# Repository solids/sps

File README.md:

sps
===

solids pressure sensitive buttons

## brain
[This is](https://github.com/solids/sps/blob/master/brain/brain.ino) an arduino sketch running on an arduino uno

## circuit

[This is] (https://github.com/solids/sps/tree/master/circuit) the latest board/schematic sensor design (designed in eagle)

## node

[This is] (https://github.com/solids/sps/tree/master/node) the code that runs on the physical board defined in the circuit folder.

Currently I2C is used for the bus, but we may migrate to chained SPI for less protocol
overhead.

## License

[MIT](http://tmpvar.mit-license.org)

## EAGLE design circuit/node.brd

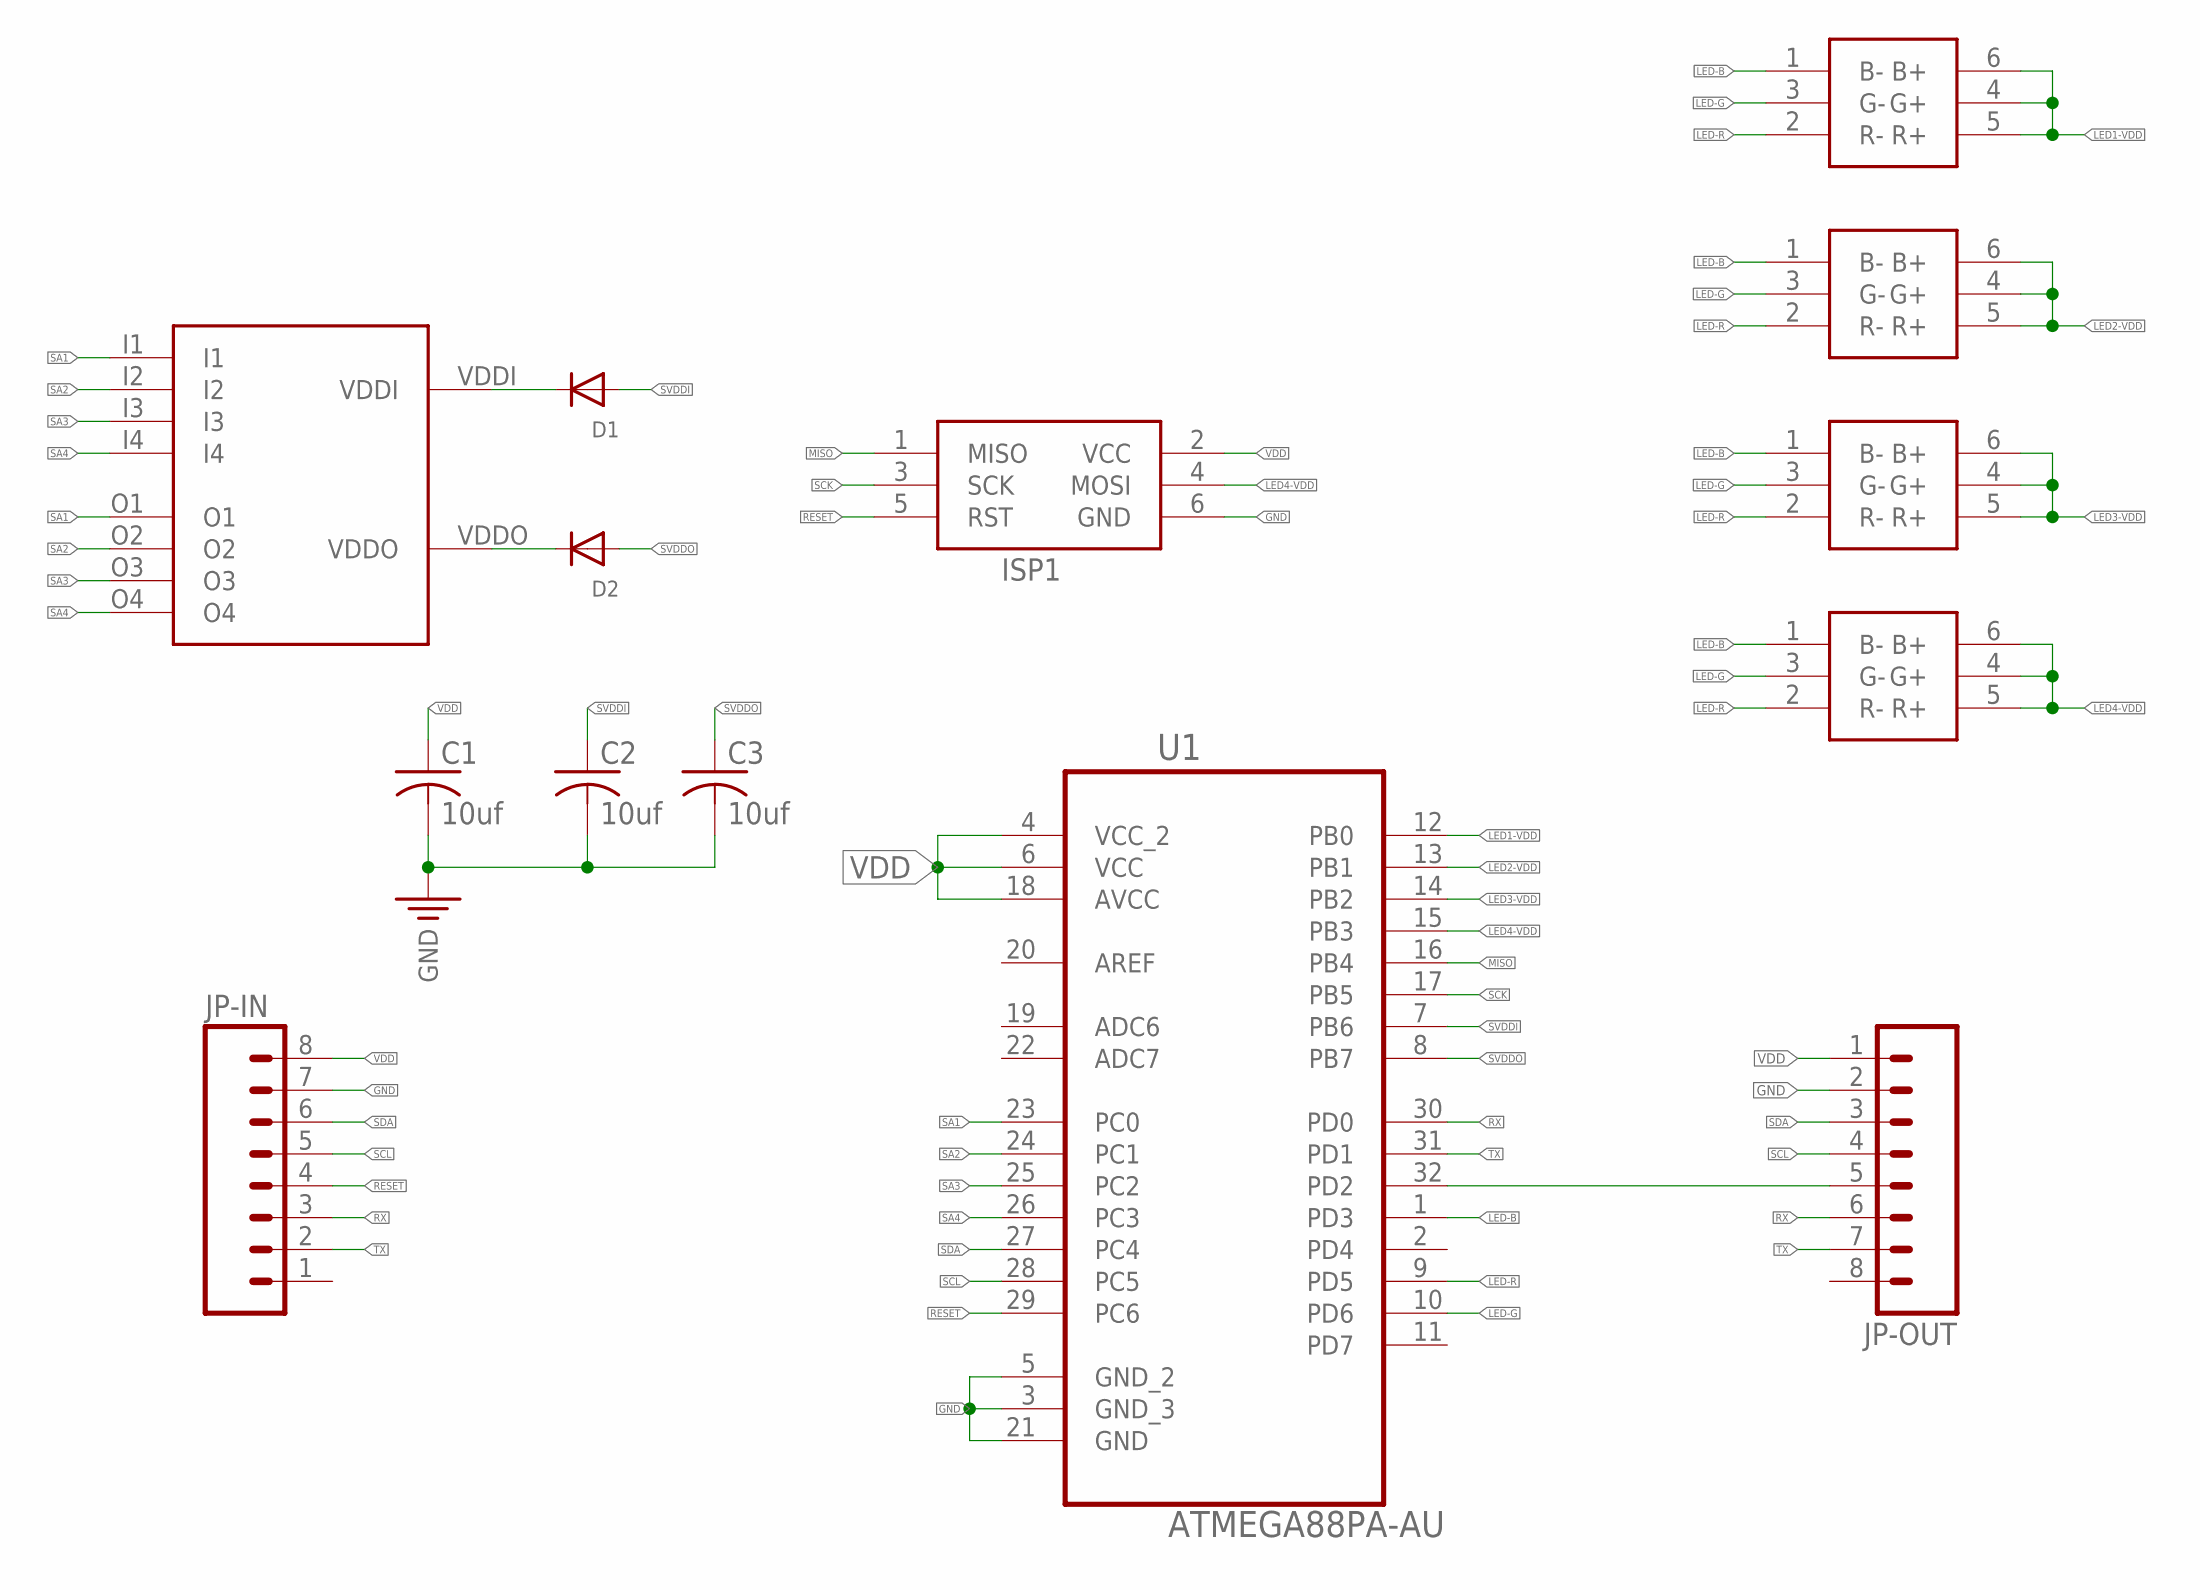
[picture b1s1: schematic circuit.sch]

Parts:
C1, C2, C3: 10uf; C0805K
D1, D2: DIODESOD-323F; SOD-323F
ISP1: AVRISP-6; AVRISP
JP-IN: M08LONGPADS; 1X08_LONGPADS
JP-OUT: M08LONGPADS; 1X08_LONGPADS
LED1, LED2, LED3, LED4: SMT-RGB-6PLCC
U1: ATMEGA88PA-AU; QFP80P900X900X120-32N
U$2: SPS8-0.0.1

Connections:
GND: C1.2, C2.2, C3.2, ISP1.6 (GND), JP-IN.7, JP-OUT.2, U1.3 (GND_3), U1.5 (GND_2), U1.21 (GND)
LED1-VDD: LED1.4 (G+), LED1.5 (R+), LED1.6 (B+), U1.12 (PB0)
LED2-VDD: LED2.4 (G+), LED2.5 (R+), LED2.6 (B+), U1.13 (PB1)
LED3-VDD: LED3.4 (G+), LED3.5 (R+), LED3.6 (B+), U1.14 (PB2)
LED4-VDD: ISP1.4 (MOSI), LED4.4 (G+), LED4.5 (R+), LED4.6 (B+), U1.15 (PB3)
LED-B: LED1.1 (B-), LED2.1 (B-), LED3.1 (B-), LED4.1 (B-), U1.1 (PD3)
LED-G: LED1.3 (G-), LED2.3 (G-), LED3.3 (G-), LED4.3 (G-), U1.10 (PD6)
LED-R: LED1.2 (R-), LED2.2 (R-), LED3.2 (R-), LED4.2 (R-), U1.9 (PD5)
MISO: ISP1.1 (MISO), U1.16 (PB4)
unnamed: D1.C, U$2.VDDI
unnamed: D2.C, U$2.VDDO
unnamed: JP-OUT.5, U1.32 (PD2)
RESET: ISP1.5 (RST), JP-IN.4, U1.29 (PC6)
RX: JP-IN.3, JP-OUT.6, U1.30 (PD0)
SA1: U1.23 (PC0), U$2.I1, U$2.O1
SA2: U1.24 (PC1), U$2.I2, U$2.O2
SA3: U1.25 (PC2), U$2.I3, U$2.O3
SA4: U1.26 (PC3), U$2.I4, U$2.O4
SCK: ISP1.3 (SCK), U1.17 (PB5)
SCL: JP-IN.5, JP-OUT.4, U1.28 (PC5)
SDA: JP-IN.6, JP-OUT.3, U1.27 (PC4)
SVDDI: C2.1, D1.A, U1.7 (PB6)
SVDDO: C3.1, D2.A, U1.8 (PB7)
TX: JP-IN.2, JP-OUT.7, U1.31 (PD1)
VDD: C1.1, ISP1.2 (VCC), JP-IN.8, JP-OUT.1, U1.4 (VCC_2), U1.6 (VCC), U1.18 (AVCC)

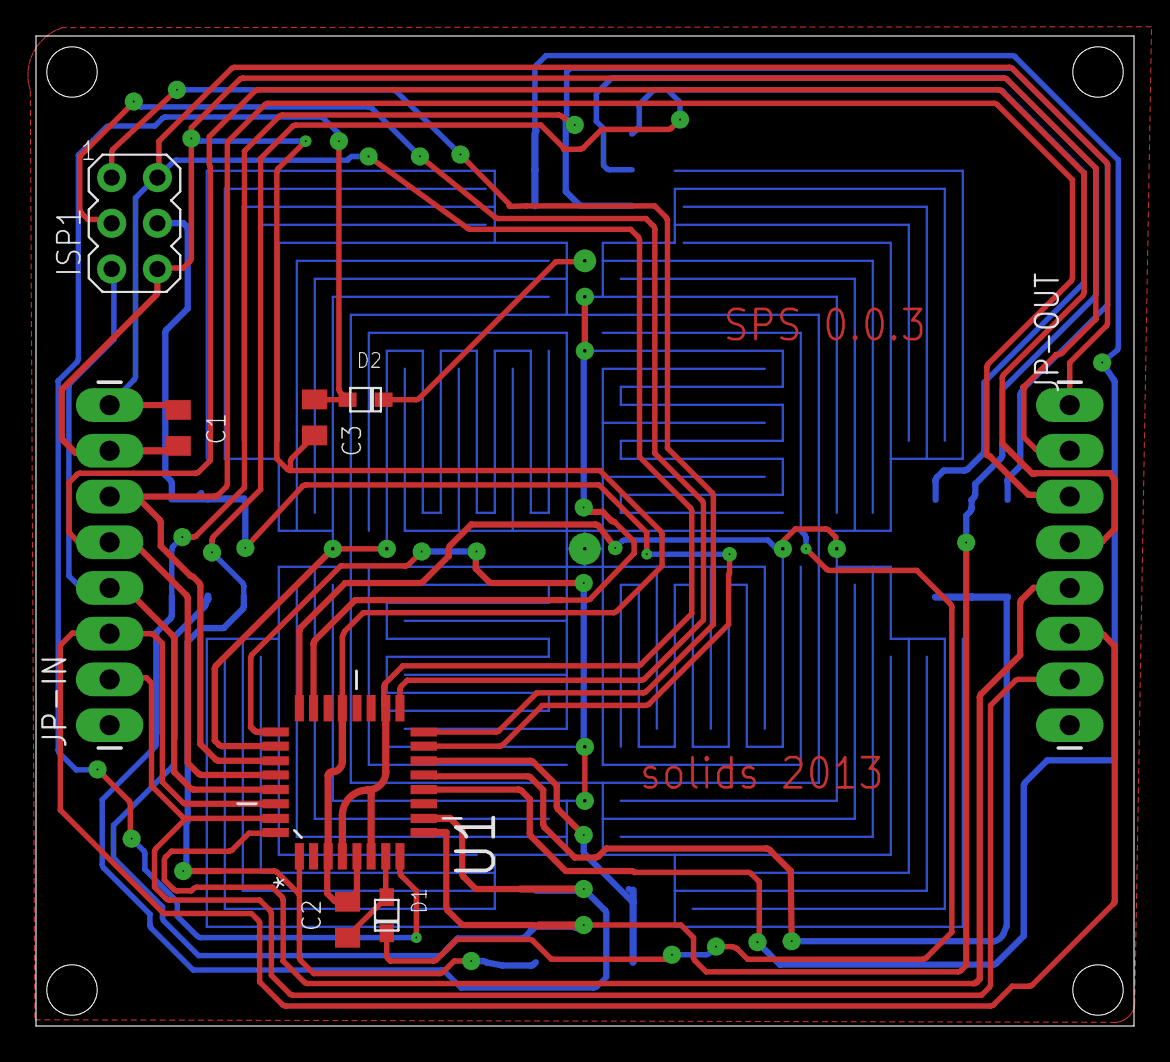
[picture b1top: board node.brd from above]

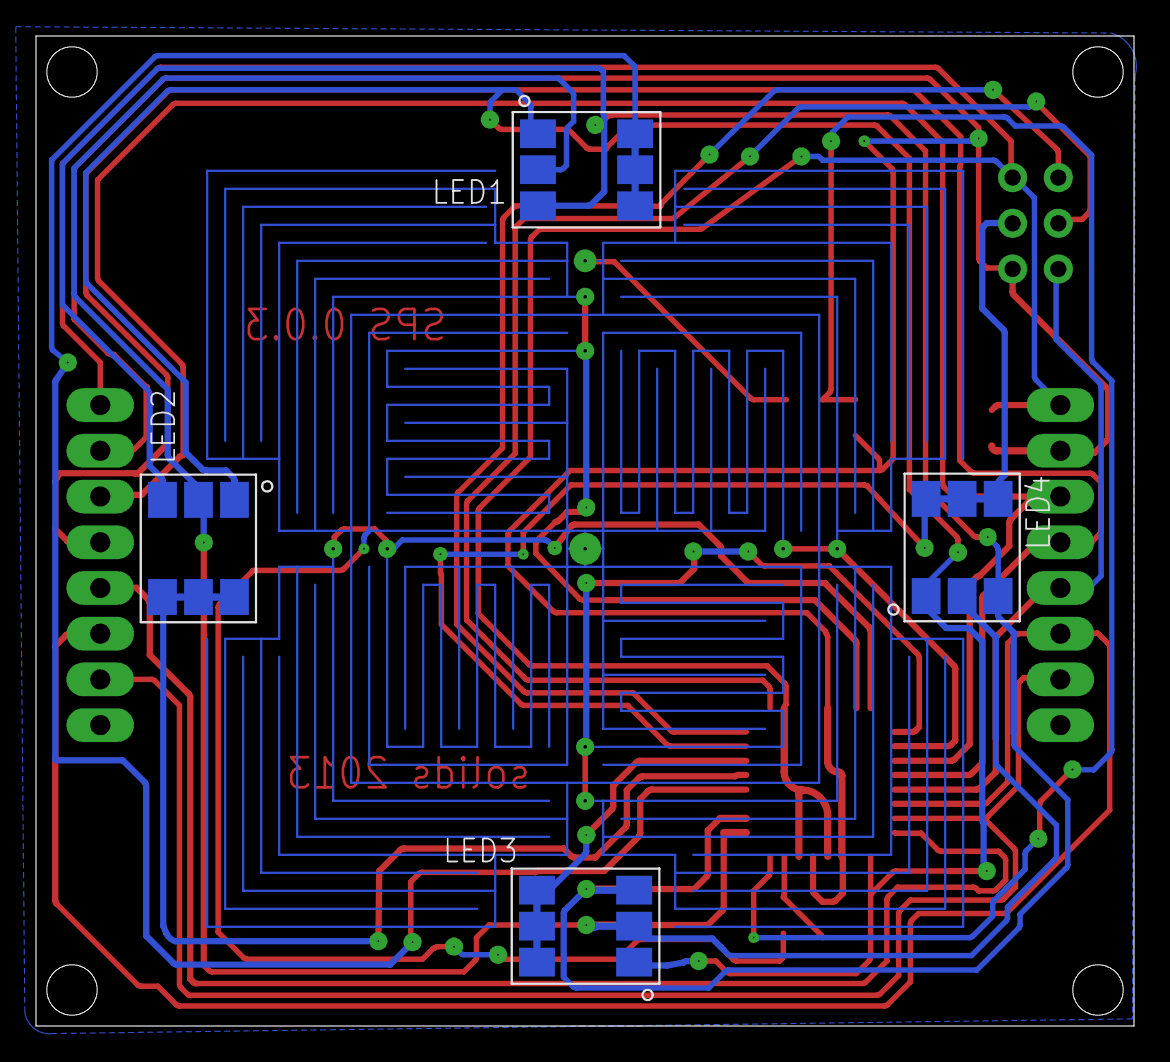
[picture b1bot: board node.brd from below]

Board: 2 copper layers, 61.0 x 55.0 mm, 14 parts (4 on the bottom side), 25 nets.

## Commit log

2013-07-21 combine all the things
2013-07-22 chain booting/addressing is functional
2013-07-22 rename 'circuit' as there will be a brain in here too
2013-07-23 add current status image
2013-07-23 Update README.md
    added missing hyperlinks
